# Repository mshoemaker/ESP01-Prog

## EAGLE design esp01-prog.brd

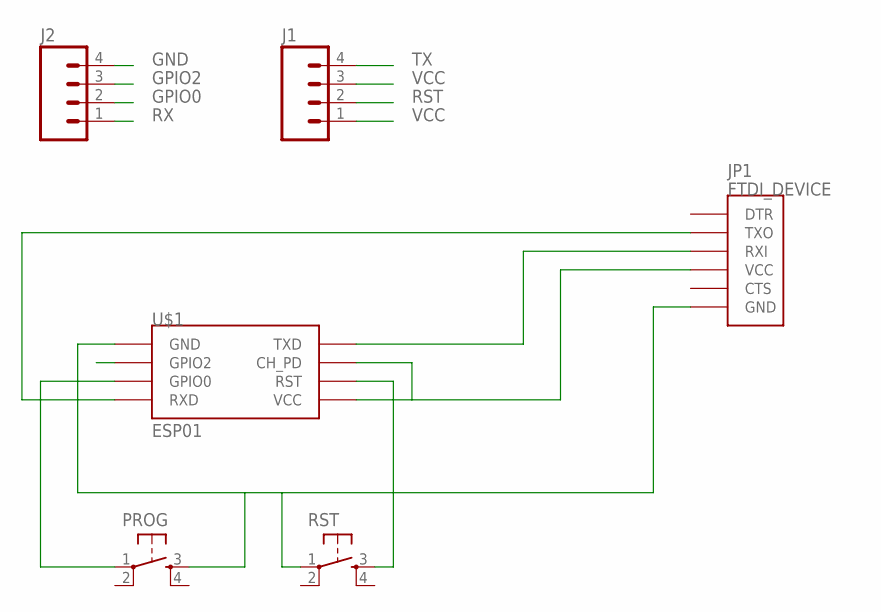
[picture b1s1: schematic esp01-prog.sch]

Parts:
J1, J2: M04PTH; 1X04
JP1: FTDI_DEVICE; FTDI_DEVICE_SIDE
PROG: TACTILE-SWITCH-PTH; TAC-SWITCH-PTH
RST: TACTILE-SWITCH-PTH; TAC-SWITCH-PTH
U$1: ESP01

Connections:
GND: J2.4, JP1.P$6 (GND), PROG.3, RST.1, U$1.GND
GPIO0: J2.2, PROG.1, U$1.GPIO0
GPIO2: J2.3, U$1.GPIO2
RST: J1.2, RST.3, U$1.RST
RX: J2.1, JP1.P$2 (TXO), U$1.RX (RXD)
TX: J1.4, JP1.P$3 (RXI), U$1.TX (TXD)
VCC: J1.1, J1.3, JP1.P$4 (VCC), U$1.CH_PD, U$1.VCC

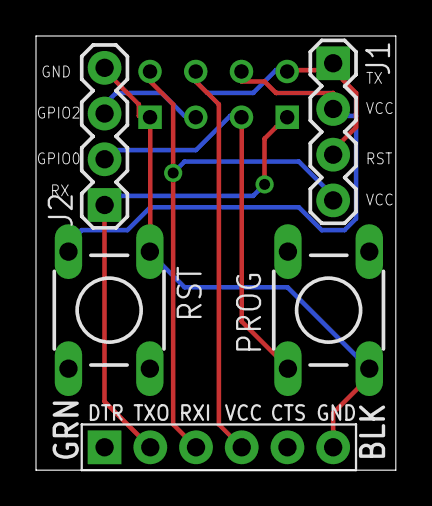
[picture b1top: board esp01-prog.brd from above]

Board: 2 copper layers, 20.0 x 24.1 mm, 6 parts (1 on the bottom side), 7 nets.

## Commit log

2016-10-20 :neckbeard: Added .gitattributes & .gitignore files
2016-10-20 Initial commit of ESP01-Prog board

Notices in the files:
parts and their libraries:
SparkFun-Connectors: Licensing: Creative Commons ShareAlike 4.0 International - https://creativecommons.org/licenses/by-sa/4.0
